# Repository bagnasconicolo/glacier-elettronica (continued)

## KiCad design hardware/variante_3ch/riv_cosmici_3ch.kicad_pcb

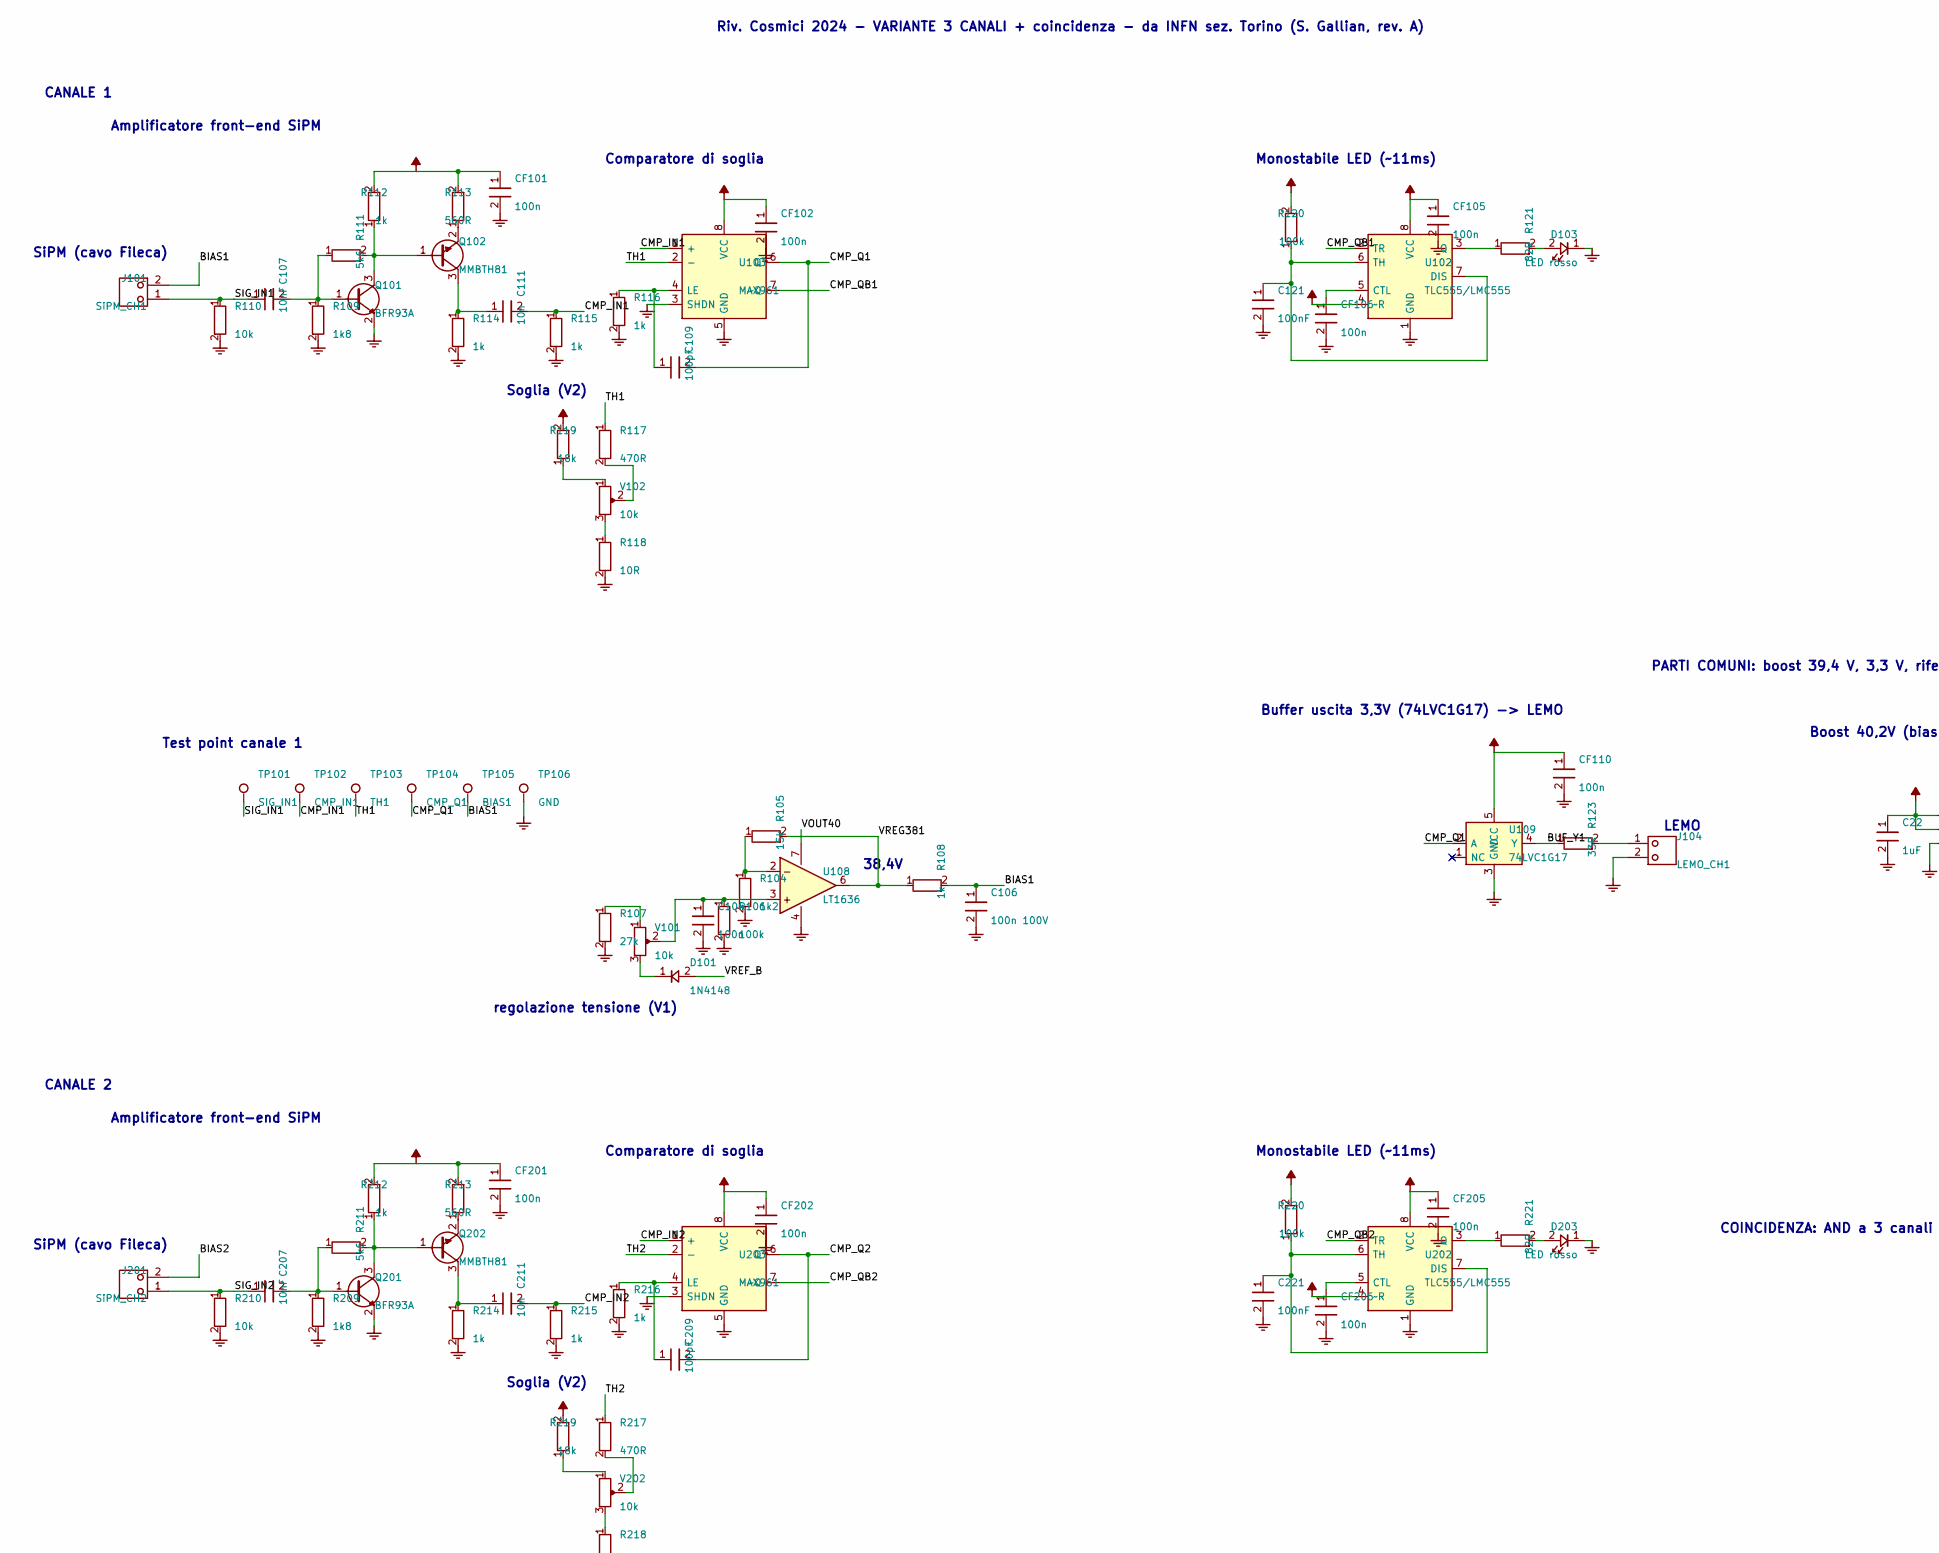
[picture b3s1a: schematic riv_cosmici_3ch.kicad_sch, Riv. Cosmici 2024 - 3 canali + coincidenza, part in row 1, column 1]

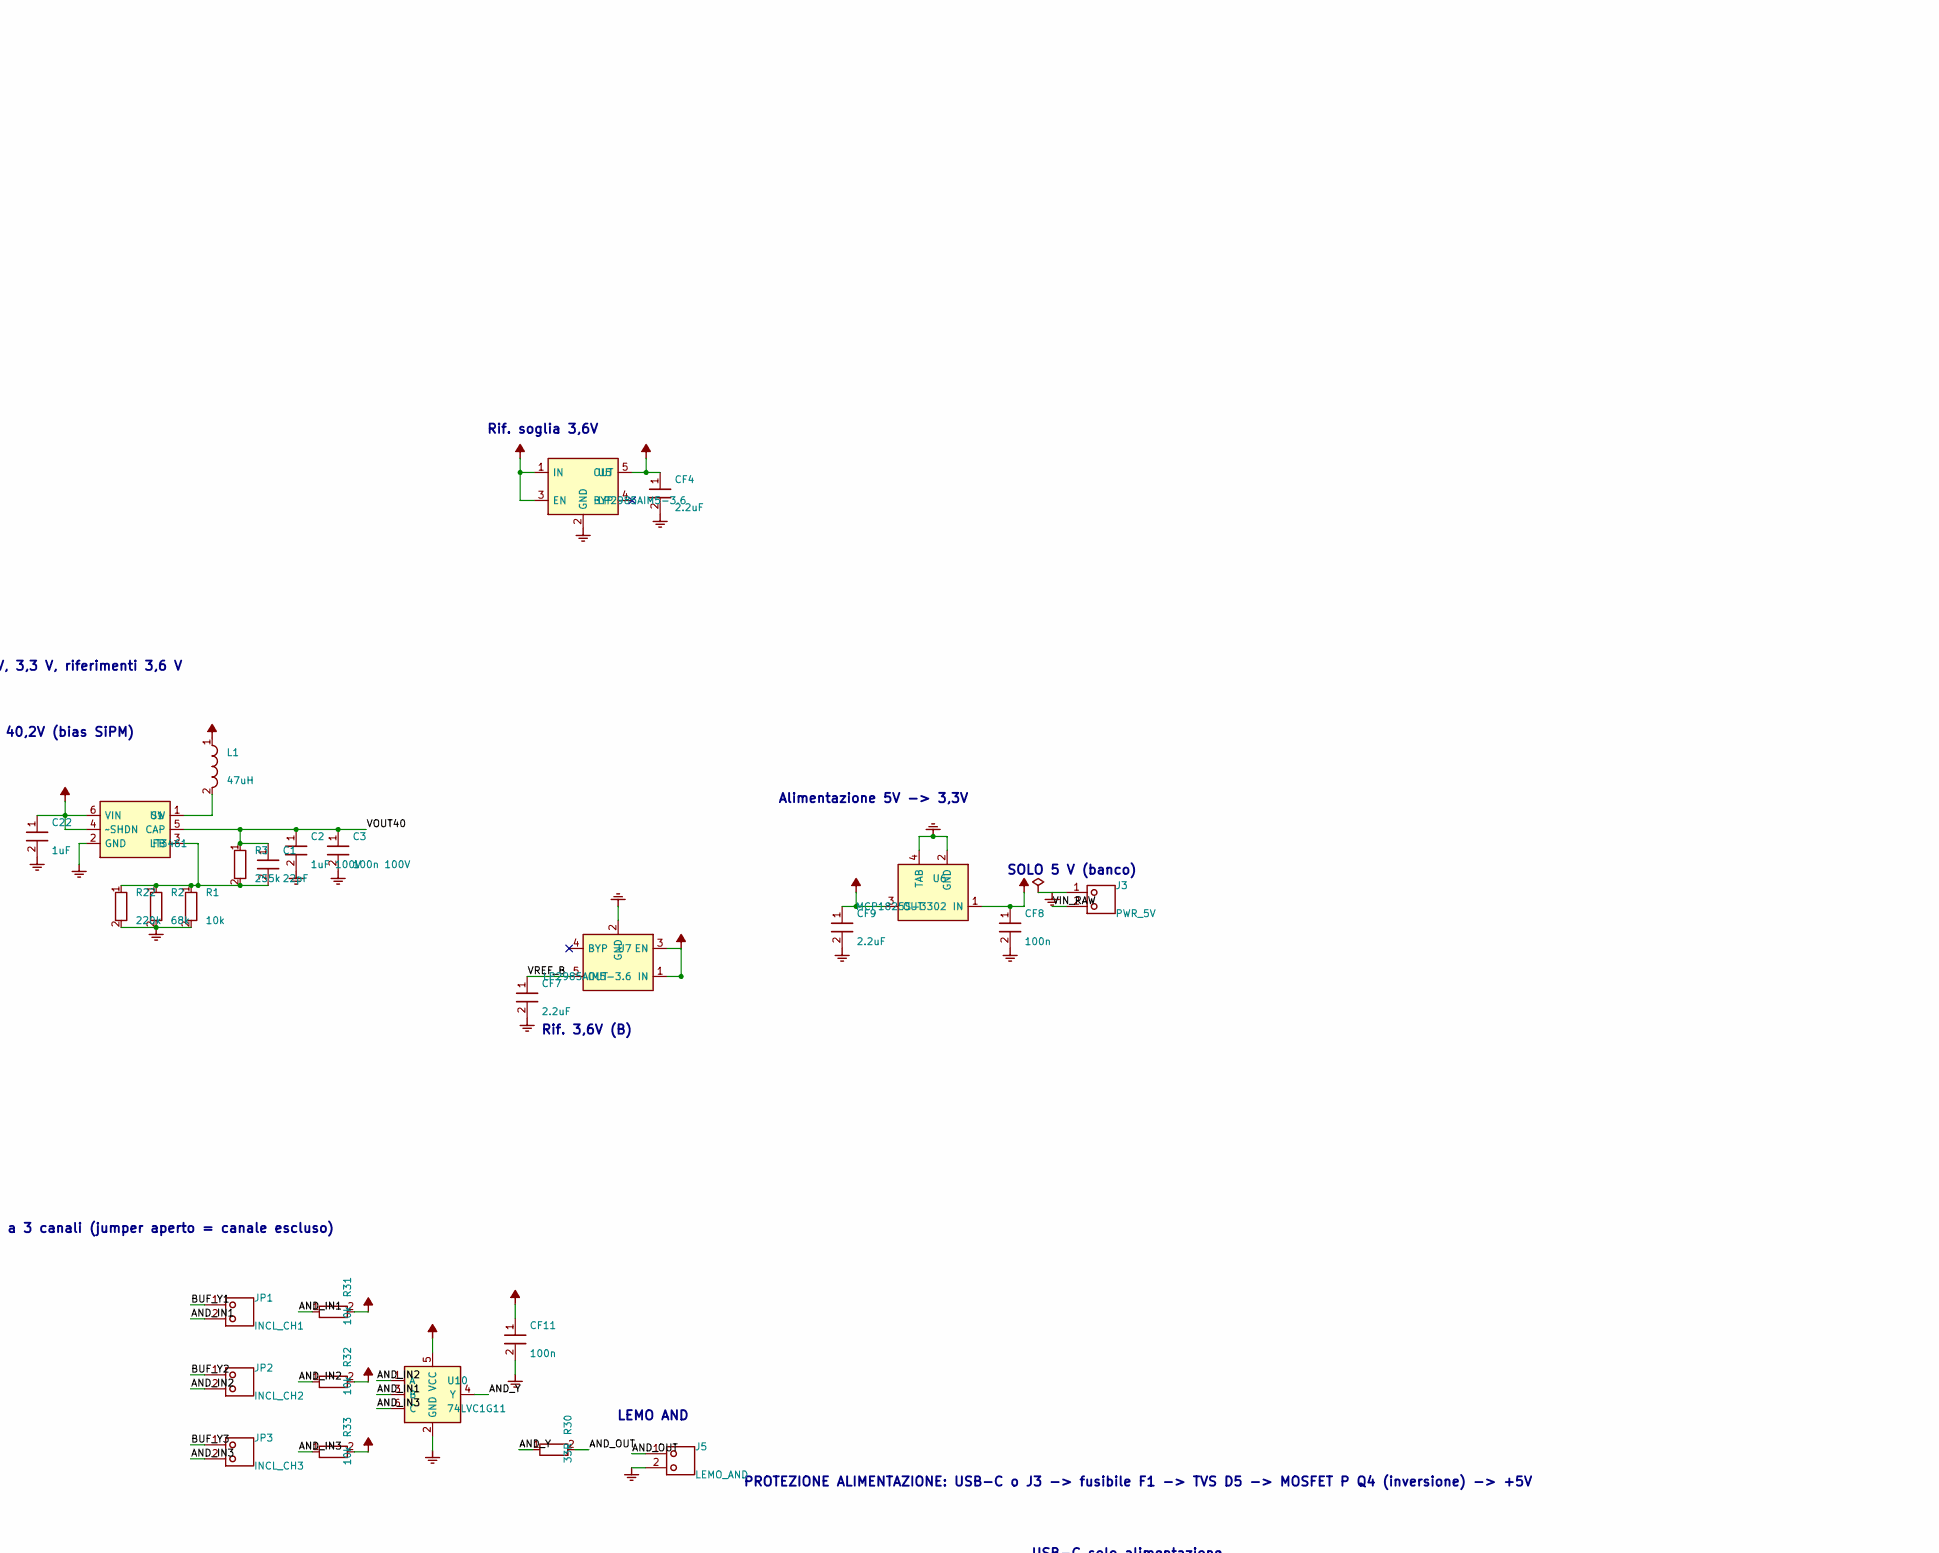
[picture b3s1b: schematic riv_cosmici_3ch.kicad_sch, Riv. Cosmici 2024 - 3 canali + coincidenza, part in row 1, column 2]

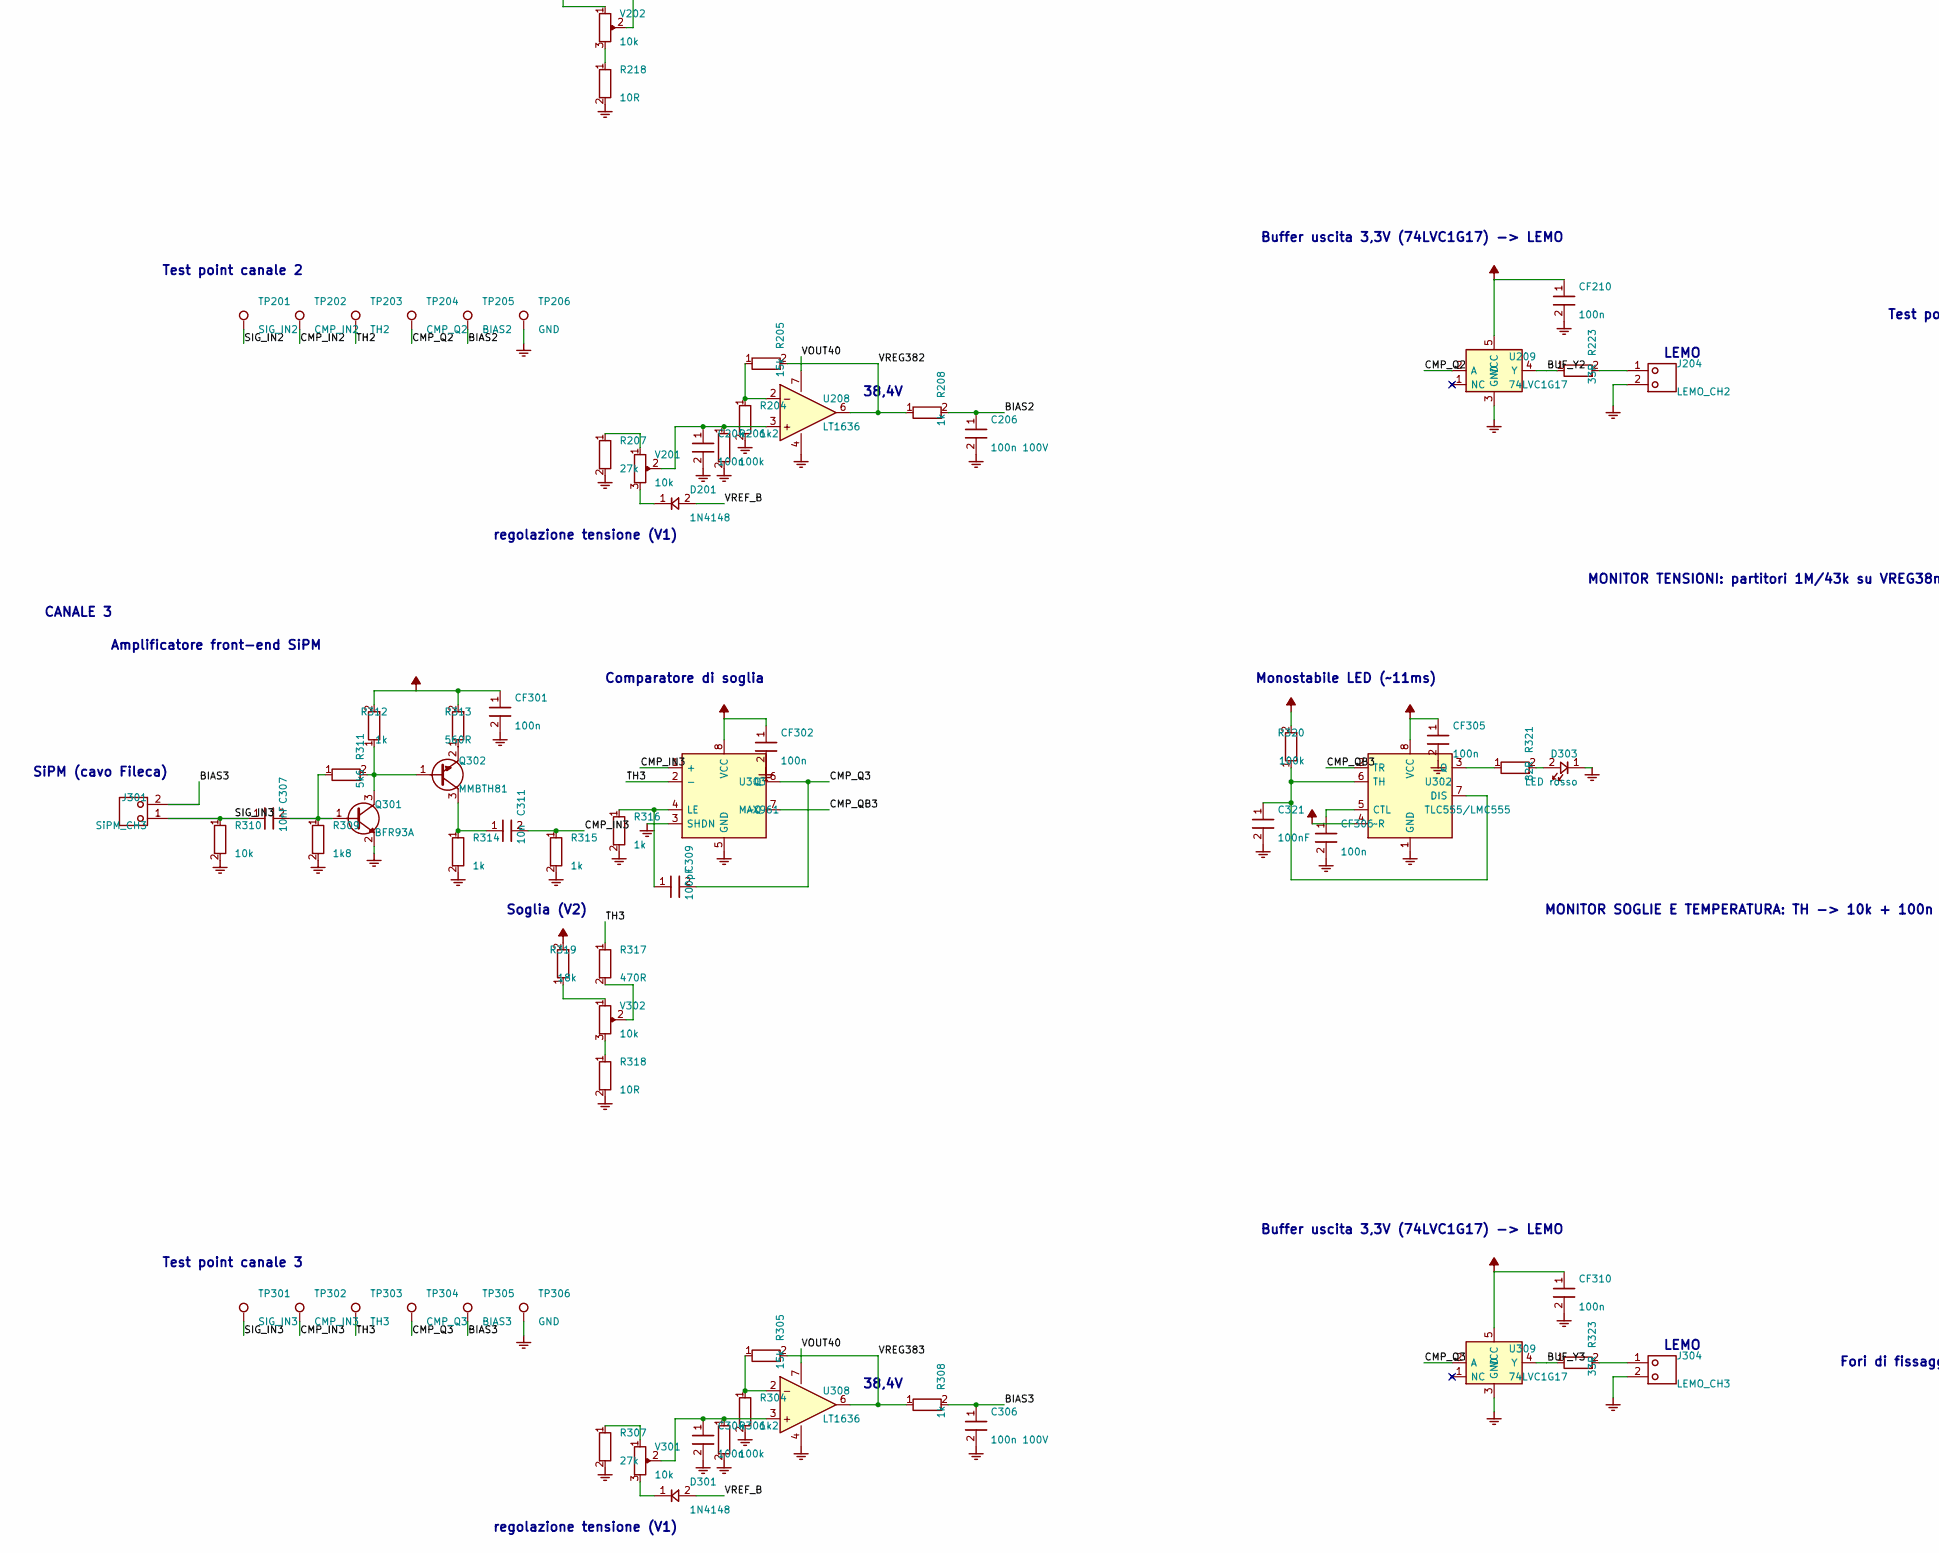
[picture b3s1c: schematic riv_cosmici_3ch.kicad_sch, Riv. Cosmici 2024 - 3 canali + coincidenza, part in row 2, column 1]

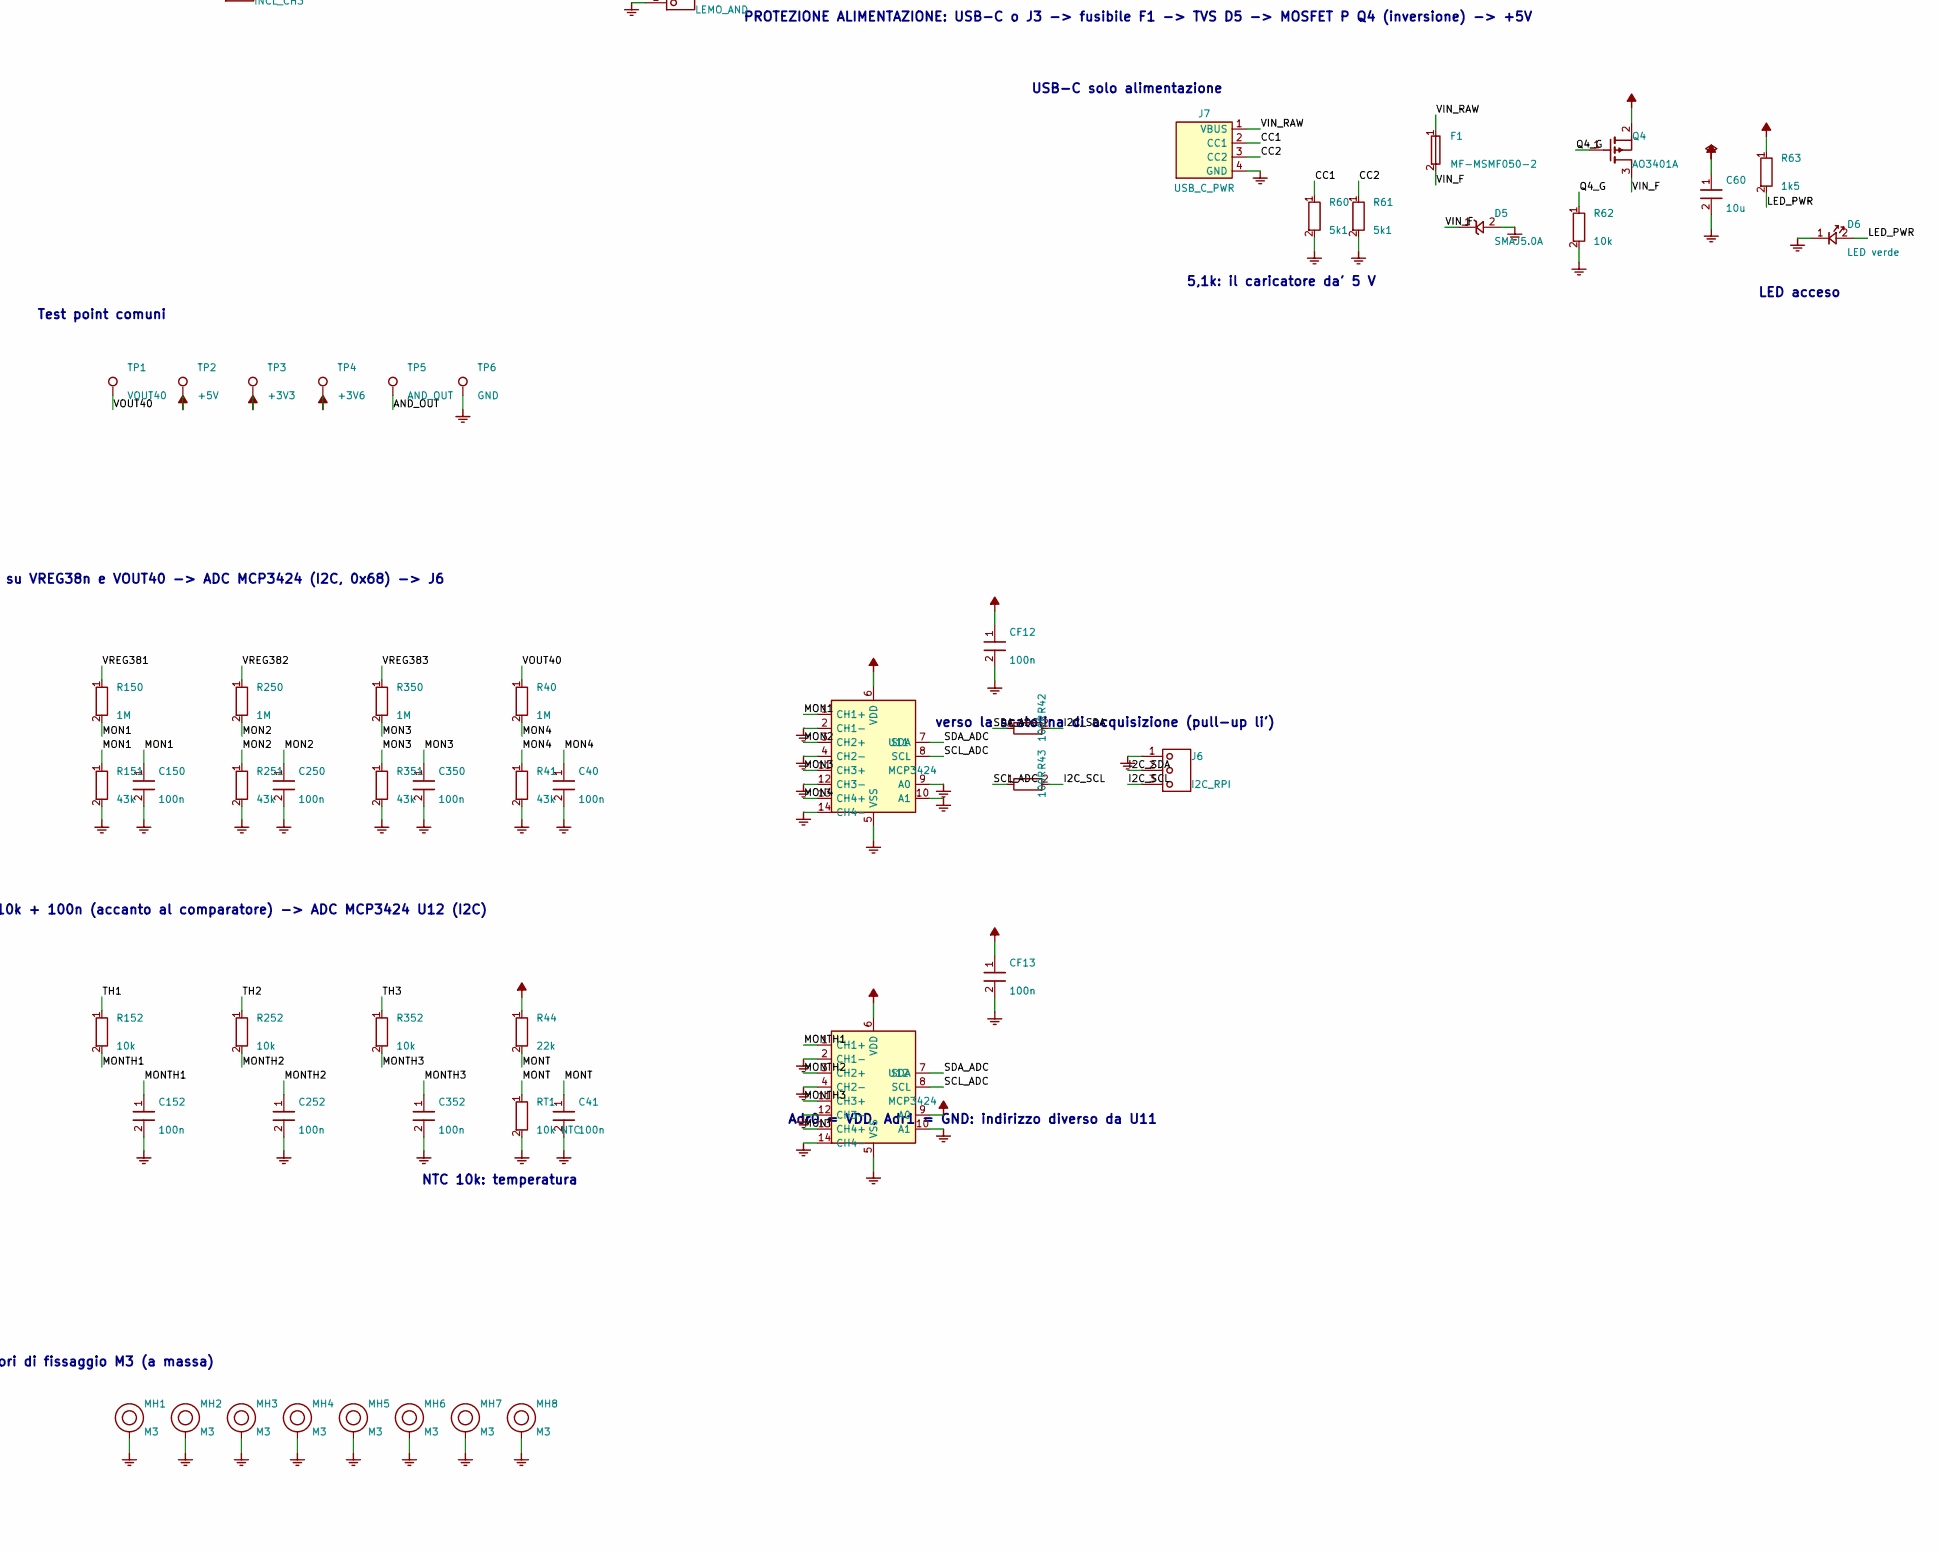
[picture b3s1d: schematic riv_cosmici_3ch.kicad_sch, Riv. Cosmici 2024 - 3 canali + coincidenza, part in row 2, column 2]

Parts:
C1: 22pF; C_0805
C2: 1uF 100V; C_1210
C3, C106, C206, C306: 100n 100V; C_1206
C22: 1uF; C_0805
C40, C41, C104, C150, C152, C204, C250, C252, C304, C350, C352: 100n; C_0805
C60: 10u; C_1206
C107, C207, C307: 10nF; C_0805
C109, C209, C309: 100pF; C_0805
C111, C211, C311: 10n; C_0805
C121, C221, C321: 100nF; C_0805
CF4, CF7, CF9: 2.2uF; C_0805
CF8, CF11, CF12, CF13, CF101, CF102, CF105, CF106, CF110, CF201, CF202, CF205, CF206, CF210, CF301, CF302, CF305, CF306, CF310: 100n; C_0805
D5: SMAJ5.0A; D_SMA
D6: LED verde; LED_0805
D101, D201, D301: 1N4148; D_DO35
D103, D203, D303: LED rosso; LED_0805
F1: MF-MSMF050-2; F_1812
J3: PWR_5V; HDR1x02
J5: LEMO_AND; LEMO_EPL00
J6: I2C_RPI; MOLEX_KK_3
J7: USB_C_PWR; USBC_GCT_USB4125
J101: SiPM_CH1; MOLEX_KK_2
J104: LEMO_CH1; LEMO_EPL00
J201: SiPM_CH2; MOLEX_KK_2
J204: LEMO_CH2; LEMO_EPL00
J301: SiPM_CH3; MOLEX_KK_2
J304: LEMO_CH3; LEMO_EPL00
JP1: INCL_CH1; HDR1x02
JP2: INCL_CH2; HDR1x02
JP3: INCL_CH3; HDR1x02
L1: 47uH; L_PWR_5050
MH1, MH2, MH3, MH4, MH5, MH6, MH7, MH8: M3; MH_M3
Q4: AO3401A; SOT23
Q101, Q201, Q301: BFR93A; SOT23
Q102, Q202, Q302: MMBTH81; SOT23
R1, R31, R32, R33, R62, R110, R152, R210, R252, R310, R352: 10k; R_0805
R2: 68k; R_0805
R3: 255k; R_0805
R22: 220k; R_0805
R30, R123, R223, R323: 33R; R_0805
R40, R150, R250, R350: 1M; R_0805
R41, R151, R251, R351: 43k; R_0805
R42, R43: 100R; R_0805
R44: 22k; R_0805
R60, R61: 5k1; R_0805
R63: 1k5; R_0805
R104, R204, R304: 1k2; R_0805
R105, R205, R305: 15k; R_0805
R106, R120, R206, R220, R306, R320: 100k; R_0805
R107, R207, R307: 27k; R_0805
R108, R112, R114, R115, R116, R208, R212, R214, R215, R216, R308, R312, R314, R315, R316: 1k; R_0805
R109, R209, R309: 1k8; R_0805
R111, R211, R311: 5k6; R_0805
R113, R213, R313: 560R; R_0805
R117, R217, R317: 470R; R_0805
R118, R218, R318: 10R; R_0805
R119, R219, R319: 18k; R_0805
R121, R221, R321: 82R; R_0805
RT1: 10k NTC; R_0805
TP1: VOUT40; TP_THT
TP2: +5V; TP_THT
TP3: +3V3; TP_THT
TP4: +3V6; TP_THT
TP5: AND_OUT; TP_THT
TP6, TP106, TP206, TP306: GND; TP_THT
TP101: SIG_IN1; TP_THT
TP102: CMP_IN1; TP_THT
TP103: TH1; TP_THT
TP104: CMP_Q1; TP_THT
TP105: BIAS1; TP_THT
TP201: SIG_IN2; TP_THT
TP202: CMP_IN2; TP_THT
TP203: TH2; TP_THT
TP204: CMP_Q2; TP_THT
TP205: BIAS2; TP_THT
TP301: SIG_IN3; TP_THT
TP302: CMP_IN3; TP_THT
TP303: TH3; TP_THT
TP304: CMP_Q3; TP_THT
TP305: BIAS3; TP_THT
U1: LT3461; SOT23-6
U5, U7: LP2985AIM5-3.6; SOT23-5
U6: MCP1825S-3302; SOT223
U10: 74LVC1G11; SOT23-6
U11, U12: MCP3424; SOIC14
U102, U202, U302: TLC555/LMC555; SOIC8
U103, U203, U303: MAX961; SOIC8
U108, U208, U308: LT1636; SOIC8
U109, U209, U309: 74LVC1G17; SOT23-5
V101, V102, V201, V202, V301, V302: 10k; TRIM_3296W

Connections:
+3V3: CF9.1, CF11.1, CF12.1, CF13.1, CF101.1, CF102.1, CF105.1, CF110.1, CF201.1, CF202.1, CF205.1, CF210.1, CF301.1, CF302.1, CF305.1, CF310.1, R31.2, R32.2, R33.2, R44.1, R112.2, R113.2, R120.2, R212.2, R213.2, R220.2, R312.2, R313.2, R320.2, TP3.1, U6.3 (OUT), U10.5 (VCC), U11.6 (VDD), U12.6 (VDD), U12.9 (A0), U102.4 (~R), U102.8 (VCC), U103.8 (VCC), U109.5 (VCC), U202.4 (~R), U202.8 (VCC), U203.8 (VCC), U209.5 (VCC), U302.4 (~R), U302.8 (VCC), U303.8 (VCC), U309.5 (VCC)
+3V6: CF4.1, R119.2, R219.2, R319.2, TP4.1, U5.5 (OUT)
+5V: C22.1, C60.1, CF8.1, L1.1, Q4.2 (S), R63.1, TP2.1, U1.4 (~SHDN), U1.6 (VIN), U5.1 (IN), U5.3 (EN), U6.1 (IN), U7.1 (IN), U7.3 (EN)
/AND_IN1: JP1.2, R31.1, U10.3 (B)
/AND_IN2: JP2.2, R32.1, U10.1 (A)
/AND_IN3: JP3.2, R33.1, U10.6 (C)
/AND_OUT: J5.1, R30.2, TP5.1
/AND_Y: R30.1, U10.4 (Y)
/BIAS1: C106.1, J101.2, R108.2, TP105.1
/BIAS2: C206.1, J201.2, R208.2, TP205.1
/BIAS3: C306.1, J301.2, R308.2, TP305.1
/BUF_Y1: JP1.1, R123.1, U109.4 (Y)
/BUF_Y2: JP2.1, R223.1, U209.4 (Y)
/BUF_Y3: JP3.1, R323.1, U309.4 (Y)
/CC1: J7.2 (CC1), R60.1
/CC2: J7.3 (CC2), R61.1
/CMP_IN1: C111.2, R115.1, TP102.1, U103.1 (+)
/CMP_IN2: C211.2, R215.1, TP202.1, U203.1 (+)
/CMP_IN3: C311.2, R315.1, TP302.1, U303.1 (+)
/CMP_Q1: C109.2, TP104.1, U103.6 (Q), U109.2 (A)
/CMP_Q2: C209.2, TP204.1, U203.6 (Q), U209.2 (A)
/CMP_Q3: C309.2, TP304.1, U303.6 (Q), U309.2 (A)
/CMP_QB1: U102.2 (TR), U103.7 (~Q)
/CMP_QB2: U202.2 (TR), U203.7 (~Q)
/CMP_QB3: U302.2 (TR), U303.7 (~Q)
/I2C_SCL: J6.3, R43.2
/I2C_SDA: J6.2, R42.2
/LED_PWR: D6.2 (A), R63.2
/MON1: C150.1, R150.2, R151.1, U11.1 (CH1+)
/MON2: C250.1, R250.2, R251.1, U11.3 (CH2+)
/MON3: C350.1, R350.2, R351.1, U11.11 (CH3+)
/MON4: C40.1, R40.2, R41.1, U11.13 (CH4+)
/MONT: C41.1, R44.2, RT1.1, U12.13 (CH4+)
/MONTH1: C152.1, R152.2, U12.1 (CH1+)
/MONTH2: C252.1, R252.2, U12.3 (CH2+)
/MONTH3: C352.1, R352.2, U12.11 (CH3+)
/Q4_G: Q4.1 (G), R62.1
/SCL_ADC: R43.1, U11.8 (SCL), U12.8 (SCL)
/SDA_ADC: R42.1, U11.7 (SDA), U12.7 (SDA)
/SIG_IN1: C107.1, J101.1, R110.1, TP101.1
/SIG_IN2: C207.1, J201.1, R210.1, TP201.1
/SIG_IN3: C307.1, J301.1, R310.1, TP301.1
/TH1: R117.1, R152.1, TP103.1, U103.2 (-)
/TH2: R217.1, R252.1, TP203.1, U203.2 (-)
/TH3: R317.1, R352.1, TP303.1, U303.2 (-)
/VIN_F: D5.1 (K), F1.2, Q4.3 (D)
/VIN_RAW: F1.1, J3.2, J7.1 (VBUS)
/VOUT40: C1.1, C2.1, C3.1, R3.1, R40.1, TP1.1, U1.5 (CAP), U108.7 (V+), U208.7 (V+), U308.7 (V+)
/VREF_B: CF7.1, D101.2 (A), D201.2 (A), D301.2 (A), U7.5 (OUT)
/VREG381: R105.2, R108.1, R150.1, U108.6
/VREG382: R205.2, R208.1, R250.1, U208.6
/VREG383: R305.2, R308.1, R350.1, U308.6
GND: C2.2, C3.2, C22.2, C40.2, C41.2, C60.2, C104.2, C106.2, C121.2, C150.2, C152.2, C204.2, C206.2, C221.2, C250.2, C252.2, C304.2, C306.2, C321.2, C350.2, C352.2, CF4.2, CF7.2, CF8.2, CF9.2, CF11.2, CF12.2, CF13.2, CF101.2, CF102.2, CF105.2, CF106.2, CF110.2, CF201.2, CF202.2, CF205.2, CF206.2, CF210.2, CF301.2, CF302.2, CF305.2, CF306.2, CF310.2, D5.2 (A), D6.1 (K), D103.1 (K), D203.1 (K), D303.1 (K), J3.1, J5.2, J6.1, J7.4 (GND), J104.2, J204.2, J304.2, MH1.1, MH2.1, MH3.1, MH4.1, MH5.1, MH6.1, MH7.1, MH8.1, Q101.2 (E), Q201.2 (E), Q301.2 (E), R1.2, R2.2, R22.2, R41.2, R60.2, R61.2, R62.2, R104.2, R106.2, R107.2, R109.2, R110.2, R114.2, R115.2, R116.2, R118.2, R151.2, R204.2, R206.2, R207.2, R209.2, R210.2, R214.2, R215.2, R216.2, R218.2, R251.2, R304.2, R306.2, R307.2, R309.2, R310.2, R314.2, R315.2, R316.2, R318.2, R351.2, RT1.2, TP6.1, TP106.1, TP206.1, TP306.1, U1.2 (GND), U5.2 (GND), U6.2 (GND), U6.4 (TAB), U7.2 (GND), U10.2 (GND), U11.2 (CH1-), U11.4 (CH2-), U11.5 (VSS), U11.9 (A0), U11.10 (A1), U11.12 (CH3-), U11.14 (CH4-), U12.2 (CH1-), U12.4 (CH2-), U12.5 (VSS), U12.10 (A1), U12.12 (CH3-), U12.14 (CH4-), U102.1 (GND), U103.3 (SHDN), U103.5 (GND), U108.4 (V-), U109.3 (GND), U202.1 (GND), U203.3 (SHDN), U203.5 (GND), U208.4 (V-), U209.3 (GND), U302.1 (GND), U303.3 (SHDN), U303.5 (GND), U308.4 (V-), U309.3 (GND)
unnamed: D101.1 (K), V101.3
unnamed: D103.2 (A), R121.2
unnamed: D201.1 (K), V201.3
unnamed: D203.2 (A), R221.2
unnamed: D301.1 (K), V301.3
unnamed: D303.2 (A), R321.2
unnamed: J104.1, R123.2
unnamed: J204.1, R223.2
unnamed: J304.1, R323.2
unnamed: C107.2, Q101.1 (B), R109.1, R111.1
unnamed: Q101.3 (C), Q102.1 (B), R111.2, R112.1
unnamed: C111.1, Q102.3 (C), R114.1
unnamed: Q102.2 (E), R113.1
unnamed: C207.2, Q201.1 (B), R209.1, R211.1
unnamed: Q201.3 (C), Q202.1 (B), R211.2, R212.1
unnamed: C211.1, Q202.3 (C), R214.1
unnamed: Q202.2 (E), R213.1
unnamed: C307.2, Q301.1 (B), R309.1, R311.1
unnamed: Q301.3 (C), Q302.1 (B), R311.2, R312.1
unnamed: C311.1, Q302.3 (C), R314.1
unnamed: Q302.2 (E), R313.1
unnamed: R107.1, V101.1
unnamed: R118.1, V102.3
unnamed: R119.1, V102.1
unnamed: R207.1, V201.1
unnamed: R218.1, V202.3
unnamed: R219.1, V202.1
unnamed: R307.1, V301.1
unnamed: R318.1, V302.3
unnamed: R319.1, V302.1
unnamed: C1.2, R1.1, R2.1, R3.2, R22.1, U1.3 (FB)
unnamed: L1.2, U1.1 (SW)
unnamed: CF106.1, U102.5 (CTL)
unnamed: C121.1, R120.1, U102.6 (TH), U102.7 (DIS)
unnamed: R121.1, U102.3 (Q)
unnamed: C109.1, R116.1, U103.4 (LE)
unnamed: C104.1, R106.1, U108.3 (+), V101.2 (W)
unnamed: R104.1, R105.1, U108.2 (-)
unnamed: CF206.1, U202.5 (CTL)
unnamed: C221.1, R220.1, U202.6 (TH), U202.7 (DIS)
unnamed: R221.1, U202.3 (Q)
unnamed: C209.1, R216.1, U203.4 (LE)
unnamed: C204.1, R206.1, U208.3 (+), V201.2 (W)
unnamed: R204.1, R205.1, U208.2 (-)
unnamed: CF306.1, U302.5 (CTL)
unnamed: C321.1, R320.1, U302.6 (TH), U302.7 (DIS)
unnamed: R321.1, U302.3 (Q)
unnamed: C309.1, R316.1, U303.4 (LE)
unnamed: C304.1, R306.1, U308.3 (+), V301.2 (W)
unnamed: R304.1, R305.1, U308.2 (-)
unnamed: R117.2, V102.2 (W)
unnamed: R217.2, V202.2 (W)
unnamed: R317.2, V302.2 (W)

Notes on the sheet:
SiPM (cavo Fileca)
Amplificatore front-end SiPM
Comparatore di soglia
Soglia (V2)
Monostabile LED (~11ms)
38,4V
regolazione tensione (V1)
Buffer uscita 3,3V (74LVC1G17) -> LEMO
LEMO
CANALE 1
Test point canale 1
CANALE 2
Test point canale 2
CANALE 3
Test point canale 3
Boost 40,2V (bias SiPM)
SOLO 5 V (banco)
Alimentazione 5V -> 3,3V
Rif. soglia 3,6V
Rif. 3,6V (B)
PARTI COMUNI: boost 39,4 V, 3,3 V, riferimenti 3,6 V
COINCIDENZA: AND a 3 canali (jumper aperto = canale escluso)
LEMO AND
Test point comuni
MONITOR TENSIONI: partitori 1M/43k su VREG38n e VOUT40 -> ADC MCP3424 (I2C, 0x68) -> J6
verso la scatolina di acquisizione (pull-up li')
MONITOR SOGLIE E TEMPERATURA: TH -> 10k + 100n (accanto al comparatore) -> ADC MCP3424 U12 (I2C)
NTC 10k: temperatura
Adr0 = VDD, Adr1 = GND: indirizzo diverso da U11
PROTEZIONE ALIMENTAZIONE: USB-C o J3 -> fusibile F1 -> TVS D5 -> MOSFET P Q4 (inversione) -> +5V
USB-C solo alimentazione
5,1k: il caricatore da' 5 V
LED acceso
Fori di fissaggio M3 (a massa)
Riv. Cosmici 2024 - VARIANTE 3 CANALI + coincidenza - da INFN sez. Torino (S. Gallian, rev. A)

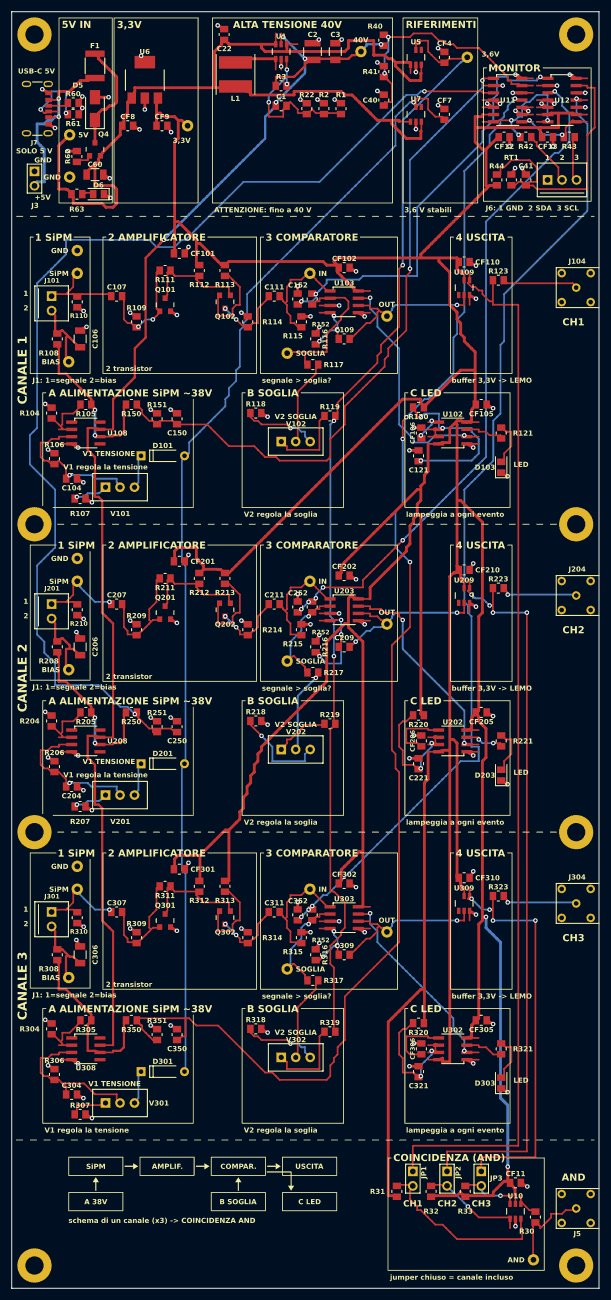
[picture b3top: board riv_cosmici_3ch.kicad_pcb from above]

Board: 2 copper layers, 103.0 x 223.9 mm, 224 parts (0 on the bottom side), 106 nets.

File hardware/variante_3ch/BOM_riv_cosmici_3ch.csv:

Rif.,Qta,Valore/Parte,Package,Codice ordine,Note
C1,1,22pF,0805,,
C2,1,1uF 100V,1210,,"dielettrico X7R, 100V (nodo VOUT40 ~41 V)"
C3 C106 C206 C306,4,100n 100V,1206,,"X7R 100V (nodi 40V/38,4V)"
C22,1,1uF,0805,,
C40 C41 C104 C150 C152 C204 C250 C252 C304 C350 C352 CF8 CF11 CF12 CF13 CF101 CF102 CF105 CF106 CF110 CF201 CF202 CF205 CF206 CF210 CF301 CF302 CF305 CF306 CF310,30,100n,0805,,X7R 50V (CF = disaccoppiamento)
C60,1,10u,1206,,"X7R 16 V (Samsung CL31B106KOHNNNE, JLCPCB C47971)"
C107 C207 C307,3,10nF,0805,,
C109 C209 C309,3,100pF,0805,,
C111 C211 C311,3,10n,0805,,
C121 C221 C321,3,100nF,0805,,
CF4 CF7 CF9,3,2.2uF,0805,,"X7R 0805 >= 10 V, es. Samsung CL21B225KAFNNNE (uscite regolatori; INFN: 100n)"
D5,1,SMAJ5.0A,SMA (DO-214AC),,"Littelfuse, TVS 5 V 400 W (JLCPCB C83329)"
D6,1,LED verde,0805,,"LED di accensione (KT-0805G, JLCPCB C2297)"
D101 D201 D301,3,1N4148,DO-35,,assiale DO-35 (o 1N4148W SOD-123 adattando il footprint)
D103 D203 D303,3,LED rosso,0805,,LED rosso 0805 (pin 1 = catodo)
F1,1,MF-MSMF050-2,1812 (4532),,"Bourns, fusibile ripristinabile 0,5 A / 15 V (JLCPCB C17313)"
J3,1,PWR_5V,Header 2.54 1x2,,"pin 1 = GND, pin 2 = +5V"
J5 J104 J204 J304,4,LEMO EPL.00.250.NTN,LEMO 00 (EPL.00.250.NTN),,presa a gomito da circuito stampato (gia' disponibili)
J6,1,I2C_RPI,Molex KK 254 3 poli (22-27-2031),,
J7,1,USB_C_PWR,USB-C 6P SMD,,"GCT USB4125-GF-A, USB-C solo alimentazione (JLCPCB C3151650)"
J101,1,SiPM_CH1,Molex KK 254 2 poli (22-27-2021),,
J201,1,SiPM_CH2,Molex KK 254 2 poli (22-27-2021),,
J301,1,SiPM_CH3,Molex KK 254 2 poli (22-27-2021),,
JP1,1,INCL_CH1,Header 2.54 1x2,,
JP2,1,INCL_CH2,Header 2.54 1x2,,
JP3,1,INCL_CH3,Header 2.54 1x2,,
L1,1,47uH,SMD 5x5/6x6,RS 693-4344,verificare l'ingombro della parte RS effettiva contro il footprint 5x5
Q4,1,AO3401A,SOT-23,,"AOS, MOSFET P -30 V contro l'inversione di polarita' (JLCPCB C15127)"
Q101 Q201 Q301,3,BFR93A,SOT-23,RS 892-2365,
Q102 Q202 Q302,3,MMBTH81,SOT-23,RS 104-1196,
R1 R31 R32 R33 R62 R110 R152 R210 R252 R310 R352,11,10k,0805,,
R2,1,68k,0805,,
R3,1,255k,0805,,"1% (INFN: 270k): VOUT40 39,4 V, sotto i 40 V max del LT3461"
R22,1,220k,0805,,
R30 R123 R223 R323,4,33R,0805,,terminazione serie del cavo verso Raspberry Pi
R40 R150 R250 R350,4,1M,0805,,partitore monitor (alto)
R41 R151 R251 R351,4,43k,0805,,partitore monitor (basso)
R42 R43,2,100R,0805,,
R44,1,22k,0805,,
R60 R61,2,5k1,0805,,CC1/CC2 dell'USB-C a massa
R63,1,1k5,0805,,LED di accensione
R104 R204 R304,3,1k2,0805,,
R105 R205 R305,3,15k,0805,,
R106 R120 R206 R220 R306 R320,6,100k,0805,,
R107 R207 R307,3,27k,0805,,
R108 R112 R114 R115 R116 R208 R212 R214 R215 R216 R308 R312 R314 R315 R316,15,1k,0805,,
R109 R209 R309,3,1k8,0805,,
R111 R211 R311,3,5k6,0805,,
R113 R213 R313,3,560R,0805,,
R117 R217 R317,3,470R,0805,,
R118 R218 R318,3,10R,0805,,
R119 R219 R319,3,18k,0805,,
R121 R221 R321,3,82R,0805,,
RT1,1,10k NTC,0805,,"termistore NTC 0805, B~3900, es. Murata NCP21XV103J03RA (temperatura scheda)"
TP1 TP2 TP3 TP4 TP5 TP6 TP101 TP102 TP103 TP104 TP105 TP106 TP201 TP202 TP203 TP204 TP205 TP206 TP301 TP302 TP303 TP304 TP305 TP306,24,test point,test point THT,,"pin di strip header 2,54 (o anello Keystone 5000 rosso / 5001 nero)"
U1,1,LT3461,SOT-23-6 (ThinSOT),Farnell 4024725,
U5 U7,2,LP2985AIM5-3.6,SOT-23-5,RS 812-2417,
U6,1,MCP1825S-3302,SOT-223,RS 669-5092,
U10,1,74LVC1G11,SOT-23-6 (ThinSOT),,"SN74LVC1G11DBVR, AND a 3 ingressi (coincidenza)"
U11 U12,2,MCP3424,SOIC-14,,"MCP3424-E/SL, ADC I2C del monitor tensioni (LCSC C640884)"
U102 U202 U302,3,TLC555/LMC555,SO-8,RS 196-2112 (LMC555CM),
U103 U203 U303,3,MAX961,SO-8,RS 189-9176,
U108 U208 U308,3,LT1636,SO-8,Farnell 4020771,
U109 U209 U309,3,74LVC1G17,SOT-23-5,,"SN74LVC1G17DBVR (TI) o equivalente; buffer 3,3 V verso Raspberry Pi"
V101 V102 V201 V202 V301 V302,6,10k,Trimmer 3296W,,Bourns 3296W-1-103LF o equivalente
(fuori scheda),3,SiPM AFBR-S4N22P014M,-,Farnell 4351470,"uno per canale, su PCB separato incollato allo scintillatore"
